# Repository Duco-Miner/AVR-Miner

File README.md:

# AVR-Miner

The AVR-Miner Board forms the Slave Device controlled by the [ESP32-Miner](https://github.com/Duco-Miner/ESP32-Miner) in the DUCO-Miner Rack. The [Common Miner Baseboard](https://github.com/Duco-Miner/Common-Miner-Baseboard) uses multiple AVR-Miner Boards for Mining the Duino Coin.

These are the KiCAD Project files for the AVR-Miner Board PCB.

Please feel free to modify the design files as per your requirements. Improvements are always appreciated !!!

---
### Preview:

1) PCB View 1:

2) PCB View 2:

3) PCB Front View:

4) PCB Back View:

---

### PCB Specifications:

- Layers: 2
- Size: 20mm x 30mm

---

### Components:

| Sr. No. | Component                               | Package | Quantity | Marking on PCB |
| :-----: | :-------------------------------------- | :-----: | :------: | :------------: |
|    1    | Atmega328P-AU or Atmega8-AU             | TQFP-32 |    1     |       U1       |
|    2    | 16MHz Crystal                           | HC49US  |    1     |       Y1       |
|    3    | 3x6x2.5mm SMD Tactile Switch            |    -    |    1     |      SW1       |
|    4    | 10uF 16V Capacitor                      |  0805   |    1     |       C5       |
|    5    | 22pF 16V Capacitor                      |  0805   |    2     |     C3,C4      |
|    6    | 0.1uF 16V Capacitor                     |  0805   |    2     |     C1,C2      |
|    7    | 10k Resistor                            |  0805   |    1     |       R1       |
|    8    | 1k Resistor                             |  0805   |    1     |       R2       |
|    9    | 1x5 2.5mm Pin Header Male - Right Angle |    -    |    1     |       J2       |
|   10    | LED (Blue Color)                        |  0805   |    1     |       D1       |

---

### Supported Controllers:

|  Controller   | Supported | Hash Rate (H/s) |
| :-----------: | :-------: | :-------------: |
| Atmega328P-AU |    ✔️     |     250-270     |
|  Atmega8-AU   |    ✔️     |     220-230     |

---

### Program/Code:

Please find the Code to be uploaded to AVR Miner here: [https://github.com/Duco-Miner/AVR-Miner-Code](https://github.com/Duco-Miner/AVR-Miner-Code)

---

### Additional Links:

- Check out the awesome Duino Coin Project at: [https://duinocoin.com](https://duinocoin.com)
- Duino Coin Wallet: [https://wallet.duinocoin.com](https://wallet.duinocoin.com)

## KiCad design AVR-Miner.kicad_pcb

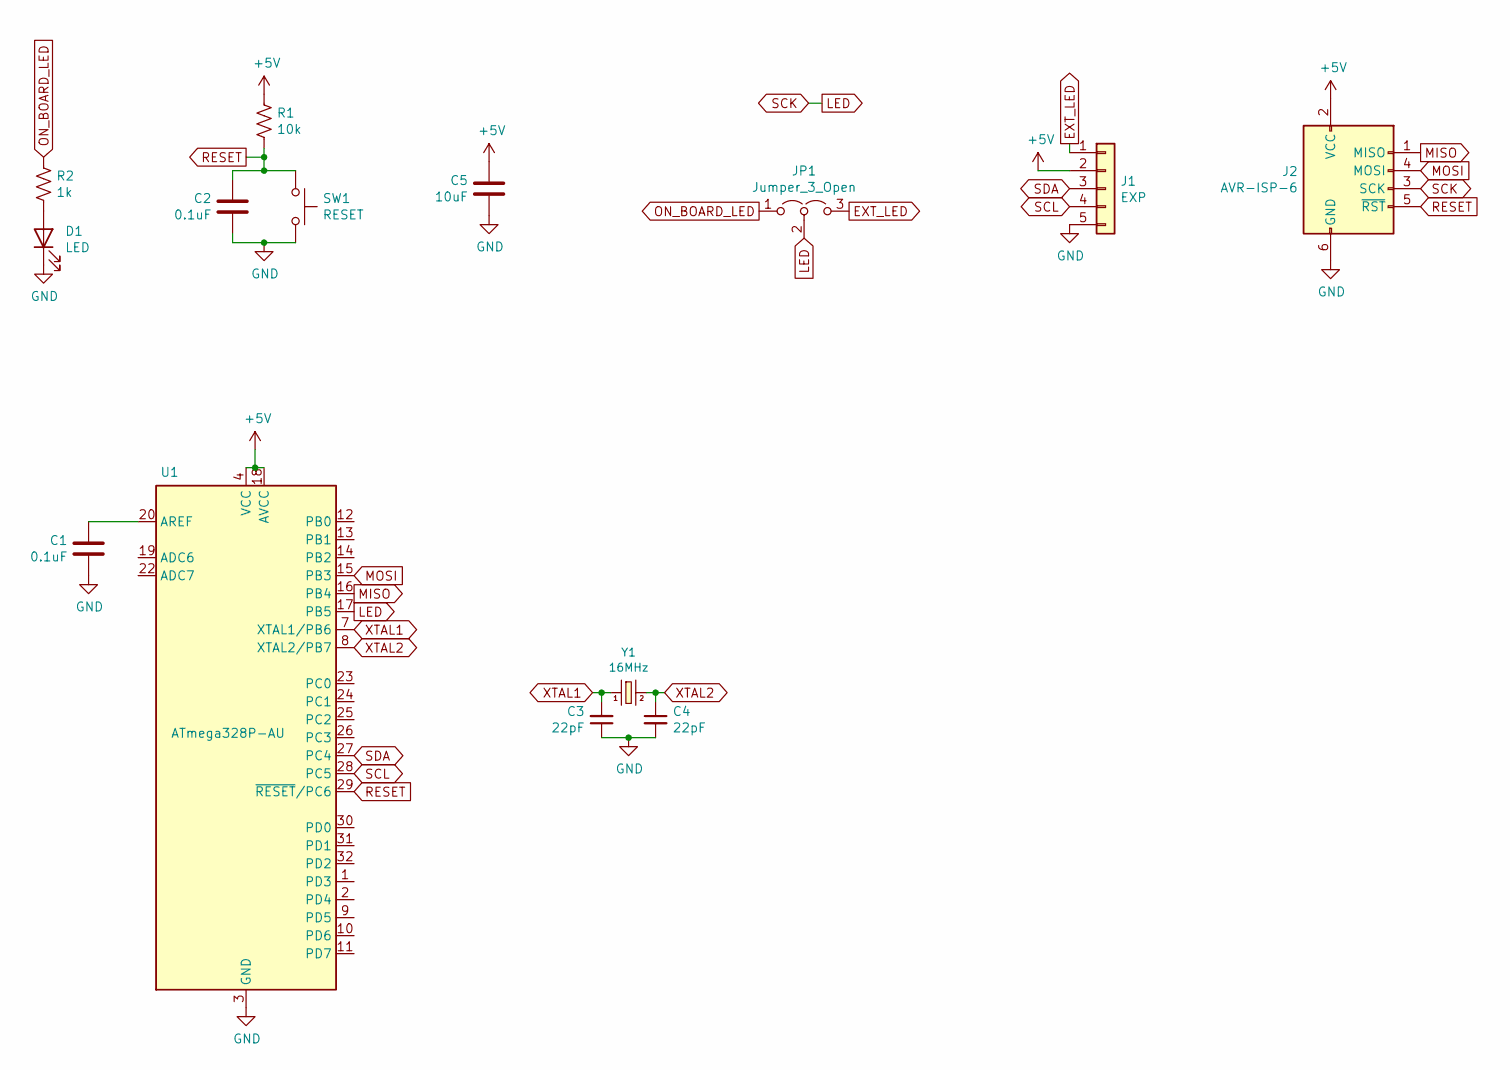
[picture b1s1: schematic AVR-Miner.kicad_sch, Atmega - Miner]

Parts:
C1, C2: 0.1uF; C_0805_2012Metric
C3, C4: 22pF; C_0805_2012Metric
C5: 10uF; C_0805_2012Metric
D1: LED; LED_0805_2012Metric
J1: EXP; PinHeader_1x05_P2.54mm_Vertical
J2: AVR-ISP-6; PinHeader_2x03_P2.54mm_Vertical
JP1: Jumper_3_Open; SolderJumper-3_P1.3mm_Open_RoundedPad1.0x1.5mm_NumberLabels
R1: 10k; R_0805_2012Metric
R2: 1k; R_0805_2012Metric
SW1: RESET; TACTILE_SWITCH_SMD_6.0X3.5MM
U1: ATmega328P-AU; TQFP-32_7x7mm_P0.8mm
Y1: 16MHz; HC49US

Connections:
+5V: C5.2, J1.2, J2.2 (VCC), R1.1, U1.4 (VCC), U1.6 (VCC), U1.18 (AVCC)
EXT_LED: J1.1, JP1.3 (B)
GND: C1.1, C2.1, C3.1, C4.2, C5.1, D1.1 (K), J1.5, J2.6 (GND), SW1.2, U1.3 (GND), U1.5 (GND), U1.21 (GND)
LED: J2.3 (SCK), JP1.2 (C), U1.17 (PB5)
MISO: J2.1 (MISO), U1.16 (PB4)
MOSI: J2.4 (MOSI), U1.15 (PB3)
unnamed: D1.2 (A), R2.2
unnamed: C1.2, U1.20 (AREF)
ON_BOARD_LED: JP1.1 (A), R2.1
RESET: C2.2, J2.5 (~RST), R1.2, SW1.1, U1.29 (~RESET/PC6)
SCL: J1.4, U1.28 (PC5)
SDA: J1.3, U1.27 (PC4)
XTAL1: C3.2, U1.7 (XTAL1/PB6), Y1.1
XTAL2: C4.1, U1.8 (XTAL2/PB7), Y1.2

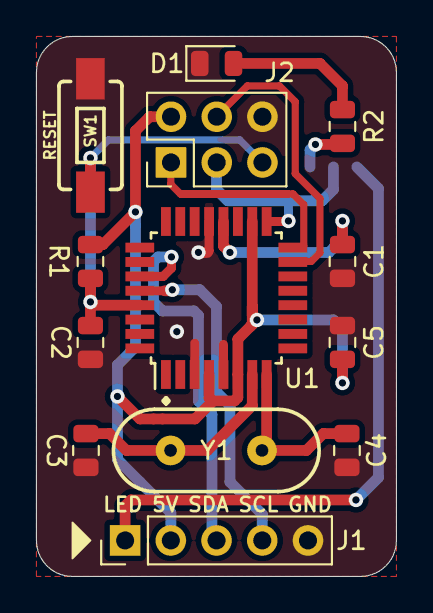
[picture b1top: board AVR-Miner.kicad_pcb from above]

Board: 2 copper layers, 20.0 x 30.0 mm, 14 parts (1 on the bottom side), 14 nets.

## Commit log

2022-05-18 Added v1.0.0
2022-05-18 Added v2.0.0
2022-05-25 Updated README & added Images for the PCB
2023-11-18 Updated project files for KiCad 7 & Added Gerber files
